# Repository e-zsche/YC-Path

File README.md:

# YC-Path

While most video synthesizers use an RGB to CVBS encoder IC for generating video signals the goal
of this project is to directly generate the luminance and chrominance signals used for analog
video signals.
of this project is to directly generate luminance and chrominance signals for analog video signals.

# System Overview

Module size specification is according to the doepfer eurorack standard.
<https://doepfer.de/a100_man/a100m_e.htm>
Module front plates are 3U in height and a multiple of 1HP wide with M3 mounting slots.

## Power Supply

The main power supply puts out ±5 V for all modules. Some older ICs run on +12V. To supply power
for these an auxilliary +12V rail is used.

First PSU Module uses Traco DC/DC Bricks. External Power is supplied via USB-C power delivery
at 20V.

TRACO TEN 10-2421:
- Vin: 18-36V
- Vout: +/- 5V
- Iout: +/- 1A

TRACO TSR 1-24120:
- Vin: 18-36V
- Vout: + 12V
- Iout: + 1A

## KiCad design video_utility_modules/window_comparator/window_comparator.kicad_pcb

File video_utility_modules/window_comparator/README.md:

# Window Comparator

Simple window comparator based on an LM319. Both thresholds are controllable by CV.

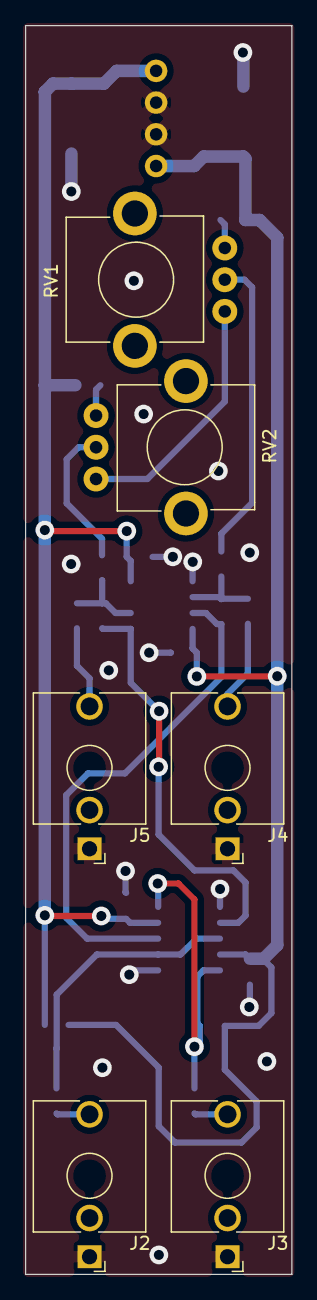
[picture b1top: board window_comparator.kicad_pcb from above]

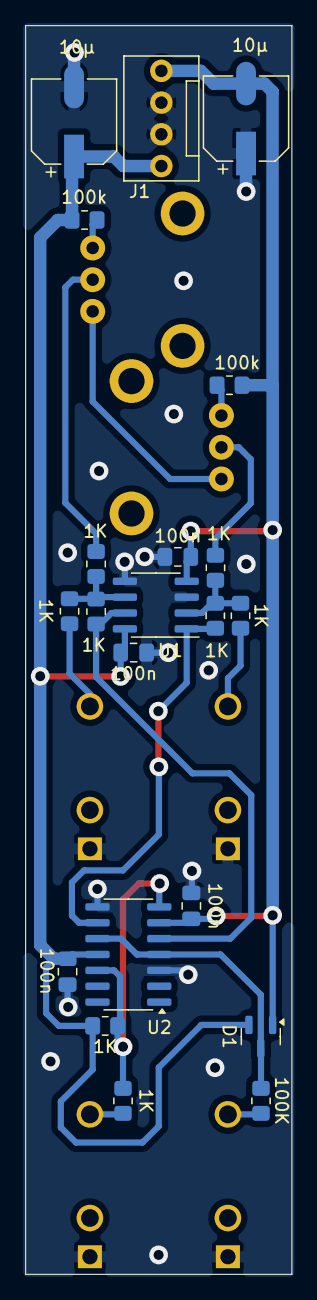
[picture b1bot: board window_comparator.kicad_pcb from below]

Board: 2 copper layers, 21.3 x 100.0 mm, 27 parts (21 on the bottom side), 18 nets.

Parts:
C1, C2, C5, C6: 100n; C_0805
C3, C4: 10µ; CP_Elec_6.3x5.3
D1: BAT54S; SOT-23
J1: pwr; pwr_conn_4pin
J2: In; Jack_3.5mm_QingPu_WQP-PJ398SM_Vertical_CircularHoles
J3: out; Jack_3.5mm_QingPu_WQP-PJ398SM_Vertical_CircularHoles
J4: CV lower; Jack_3.5mm_QingPu_WQP-PJ398SM_Vertical_CircularHoles
J5: CV upper; Jack_3.5mm_QingPu_WQP-PJ398SM_Vertical_CircularHoles
R1, R5, R9, R10, R11, R12, R13, R14: 1K; R_0805
R2, R3: 100k; R_0805
R4: 100K; R_0805
RV1, RV2: 25K; poti_stehend
U1: LMH6643; SOIC-8_no_mark
U2: LM319; SOIC-14_3.9x8.7mm_P1.27mm

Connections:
+5V: C1.1, C3.1, C5.1, D1.2 (K), J1.1, R1.1, R3.1, U1.8 (V+), U2.11 (V+)
-5V: C2.2, C4.2, C6.2, D1.1 (A), J1.4, R2.2, U1.4 (V-), U2.6 (V-)
/V_lower_pot: R12.1, RV1.2
/V_upper_pot: R14.1, RV2.2
/in: D1.3 (COM), R4.2, U2.4 (+), U2.10 (-)
/lower_tresh: R9.2, U1.7, U2.5 (-)
/out: J3.T, R5.2
/upper_tresh: R10.2, U1.1, U2.9 (+)
GND: C1.2, C2.1, C3.2, C4.1, C5.2, C6.1, J1.2, J1.3, J2.S, J3.S, J4.S, J5.S, U1.3 (+), U1.5 (+), U2.3 (GND), U2.8 (GND)
unnamed: J2.T, R4.1
unnamed: J4.T, R11.1
unnamed: J5.T, R13.1
unnamed: R1.2, R5.1, U2.7, U2.12
unnamed: R2.1, RV2.1
unnamed: R3.2, RV1.3
unnamed: RV1.1, RV2.3
unnamed: R10.1, R13.2, R14.2, U1.2 (-)
unnamed: R9.1, R11.2, R12.2, U1.6 (-)

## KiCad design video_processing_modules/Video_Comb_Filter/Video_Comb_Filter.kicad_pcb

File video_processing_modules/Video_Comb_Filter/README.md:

# Video Comb Filter

This module filters Luma and Chroma from an incoming CVBS signal. The filter is the obsolete
video IC SAA4960.

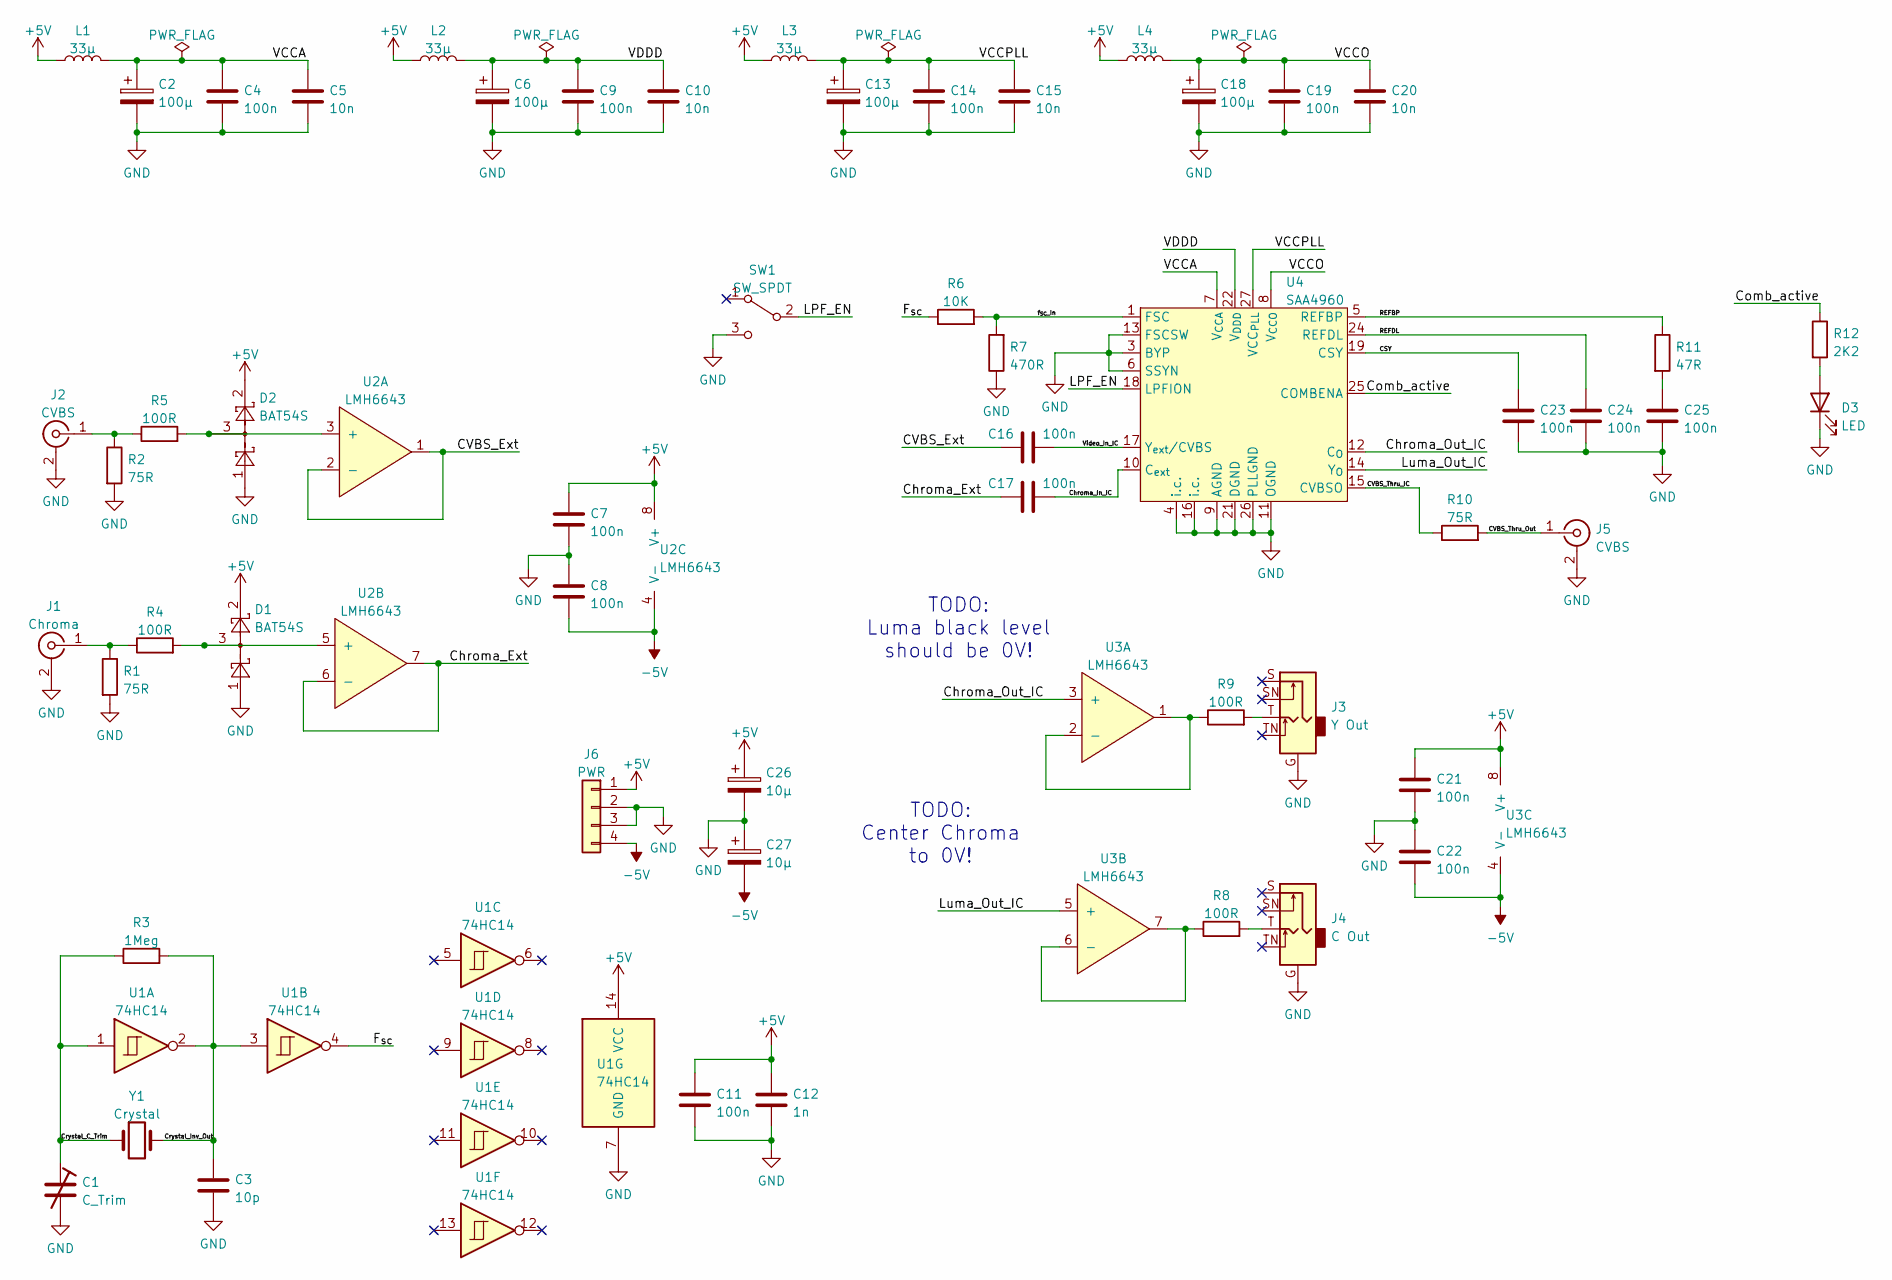
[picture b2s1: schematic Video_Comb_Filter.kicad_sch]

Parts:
C1: C_Trim
C2, C6, C13, C18: 100µ; CP_Radial_D8.0mm_P3.50mm
C3: 10p; C_0805
C4, C7, C8, C9, C11, C14, C16, C17, C19, C21, C22, C23, C24, C25: 100n; C_0805
C5, C10, C15, C20: 10n; C_0805
C12: 1n; C_0805
C26, C27: 10µ; CP_Radial_D8.0mm_P3.50mm
D1, D2: BAT54S; SOT-23
D3: LED; LED_D5.0mm
J1: Chroma; Cinch_Gewinkelt
J2: CVBS; Cinch_Gewinkelt
J3: Y Out; 3_5_mm_Buchse_EBS_35
J4: C Out; 3_5_mm_Buchse_EBS_35
J5: CVBS; BNC_Free
J6: PWR; pwr_conn_4pin
L1, L2, L3, L4: 33µ; Bourns SRN5040-330M
R1, R2, R10: 75R; R_0805
R3: 1Meg; R_0805
R4, R5, R8, R9: 100R; R_0805
R6: 10K; R_0805
R7: 470R; R_0805
R11: 47R; R_0805
R12: 2K2; R_0805
SW1: SW_SPDT; Schalter
U1: 74HC14; SOIC-14_no_mark
U2, U3: LMH6643; SOIC-8_no_mark
U4: SAA4960; DIP-28_W15.24mm_LongPads
Y1: Crystal; Crystal_HC49-U_Vertical

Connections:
+5V: C7.1, C11.1, C12.1, C21.1, C26.1, D1.2, D2.2, J6.1, L1.1, L2.1, L3.1, L4.1, U1.14 (VCC), U2.8 (V+), U3.8 (V+)
-5V: C8.2, C22.2, C27.2, J6.4, U2.4 (V-), U3.4 (V-)
/CSY: C23.1, U4.19 (CSY)
/CVBS_Ext: C16.1, U2.1, U2.2 (-)
/CVBS_Thru_IC: R10.1, U4.15 (CVBSO)
/CVBS_Thru_Out: J5.1 (In), R10.2
/Chroma_Ext: C17.1, U2.6 (-), U2.7
/Chroma_In_IC: C17.2, U4.10 (C_{ext})
/Chroma_Out_IC: U3.3 (+), U4.12 (C_{O})
/Comb_active: R12.1, U4.25 (COMBENA)
/Crystal_C_Trim: C1.1, R3.1, U1.1, Y1.1
/Crystal_Inv_Out: C3.1, R3.2, U1.2, U1.3, Y1.2
/F_{sc}: R6.1, U1.4
/LPF_EN: SW1.2 (B), U4.18 (LPFION)
/Luma_Out_IC: U3.5 (+), U4.14 (Y_{O})
/REFBP: R11.1, U4.5 (REFBP)
/REFDL: C24.1, U4.24 (REFDL)
/VCCA: C2.1, C4.1, C5.1, L1.2, U4.7 (V_{CCA})
/VCCO: C18.1, C19.1, C20.1, L4.2, U4.8 (V_{CCO})
/VCCPLL: C13.1, C14.1, C15.1, L3.2, U4.27 (VCC_{PLL})
/VDDD: C6.1, C9.1, C10.1, L2.2, U4.22 (V_{DDD})
/Video_In_IC: C16.2, U4.17 (Y_{ext}/CVBS)
/f_{SC}_In: R6.2, R7.2, U4.1 (FSC)
GND: C1.2, C2.2, C3.2, C4.2, C5.2, C6.2, C7.2, C8.1, C9.2, C10.2, C11.2, C12.2, C13.2, C14.2, C15.2, C18.2, C19.2, C20.2, C21.2, C22.1, C23.2, C24.2, C25.2, C26.2, C27.1, D1.1, D2.1, D3.1 (K), J1.2 (Ext), J2.2 (Ext), J3.G, J4.G, J5.2 (Ext), J6.2, J6.3, R1.2, R2.2, R7.1, SW1.3 (C), U1.7 (GND), U4.3 (BYP), U4.4 (i.c.), U4.6 (SSYN), U4.9 (AGND), U4.11 (OGND), U4.13 (FSCSW), U4.16 (i.c.), U4.21 (DGND), U4.26 (PLLGND)
unnamed: C25.1, R11.2
unnamed: D1.3, R4.2, U2.5 (+)
unnamed: D2.3, R5.2, U2.3 (+)
unnamed: D3.2 (A), R12.2
unnamed: J1.1 (In), R1.1, R4.1
unnamed: J2.1 (In), R2.1, R5.1
unnamed: J3.T, R9.2
unnamed: J4.T, R8.2
unnamed: R8.1, U3.6 (-), U3.7
unnamed: R9.1, U3.1, U3.2 (-)

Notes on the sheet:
TODO: Center Chroma to 0V!
TODO: Luma black level should be 0V!

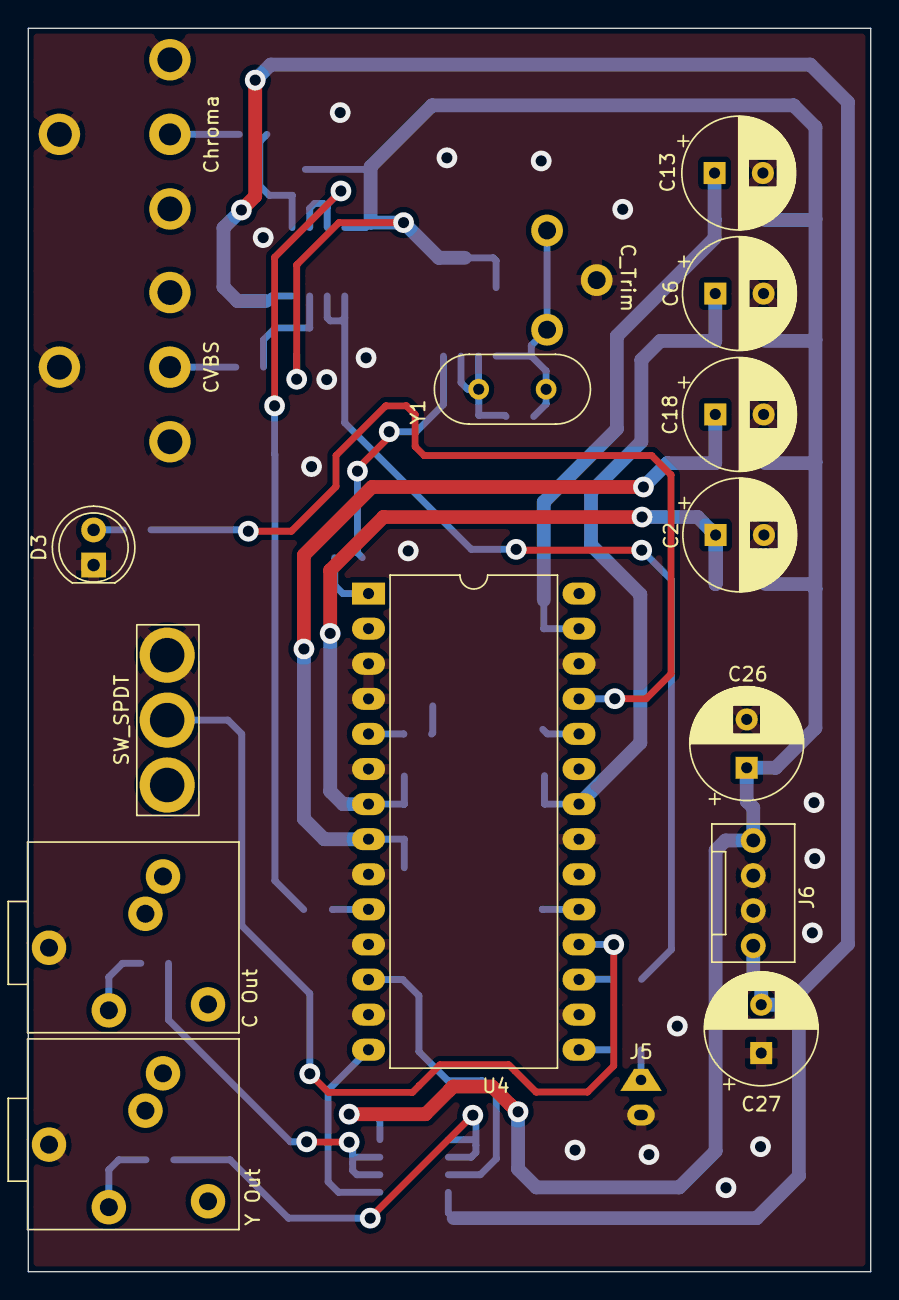
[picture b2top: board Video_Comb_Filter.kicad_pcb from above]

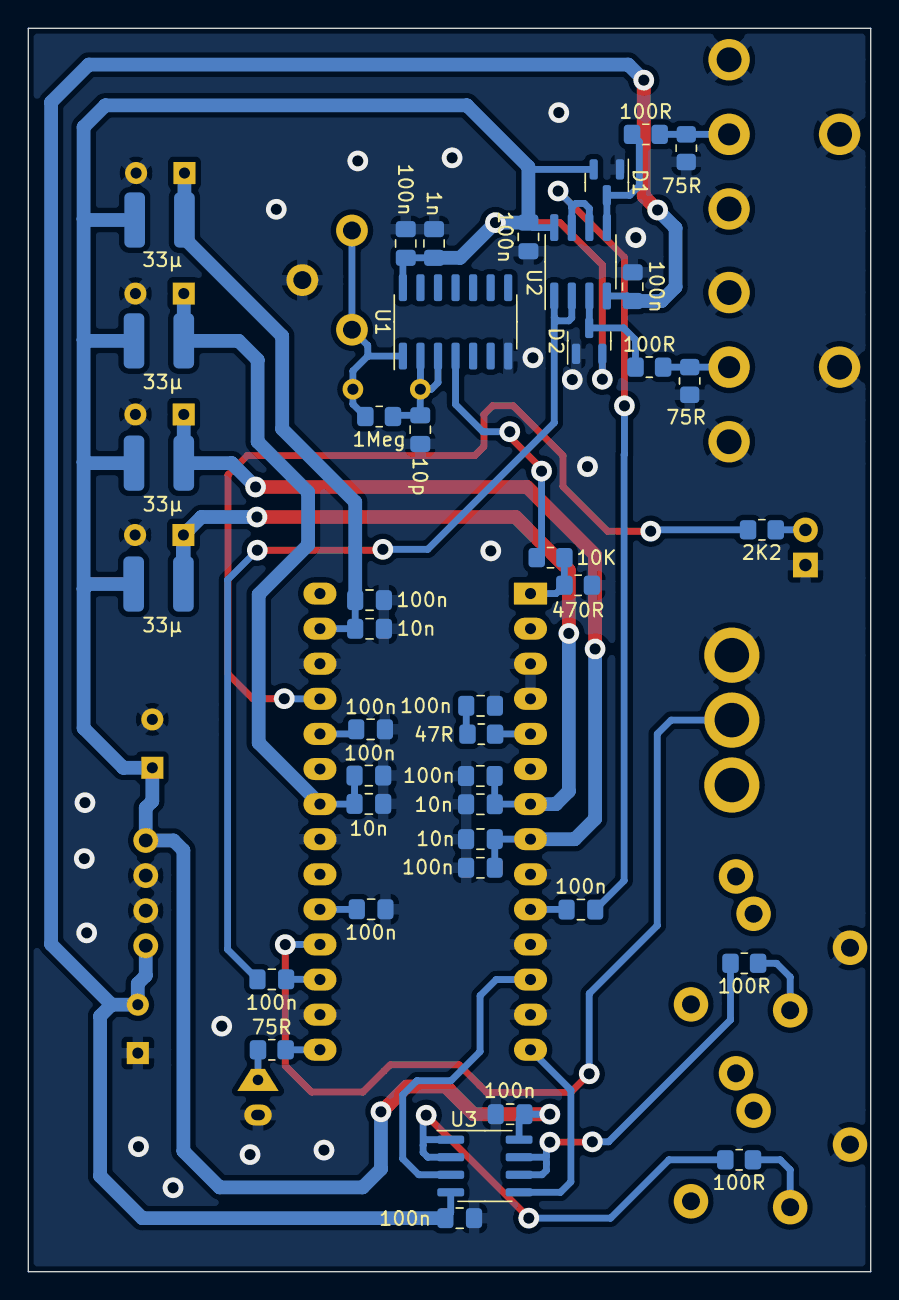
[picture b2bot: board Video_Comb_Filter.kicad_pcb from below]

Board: 2 copper layers, 61.0 x 90.0 mm, 58 parts (41 on the bottom side), 34 nets.

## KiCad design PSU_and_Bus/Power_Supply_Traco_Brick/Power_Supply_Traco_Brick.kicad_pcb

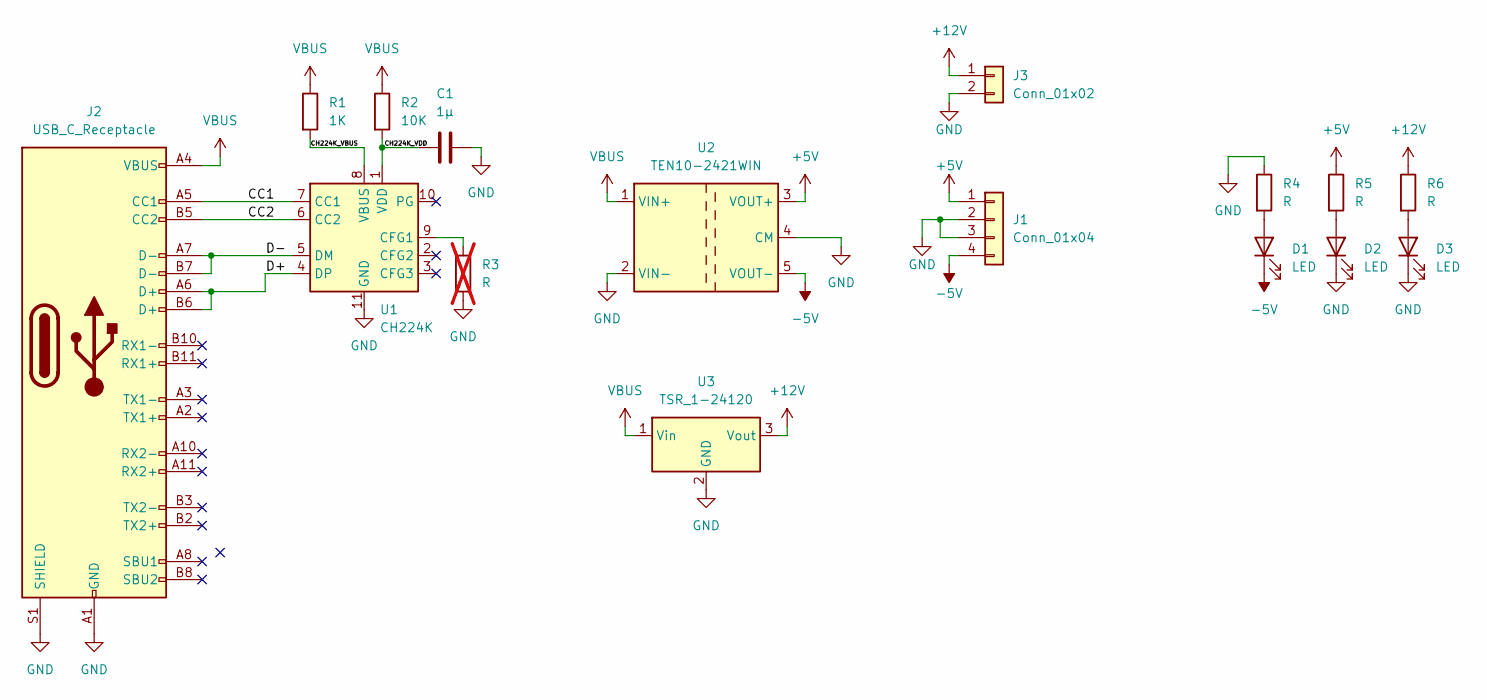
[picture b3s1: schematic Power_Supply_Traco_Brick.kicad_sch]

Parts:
C1: 1µ; C_0805
D1, D2, D3: LED; LED_D5.0mm
J1: Conn_01x04; PinHeader_1x04_P2.54mm_Vertical
J2: USB_C_Receptacle; USB_C_Receptacle_JAE_DX07S024WJ1R350
J3: Conn_01x02; PinHeader_1x02_P2.54mm_Vertical
R1: 1K; R_0805
R2: 10K; R_0805
R3: R; R_0805; not fitted
R4, R5, R6: R; R_0805
U1: CH224K; SSOP-10-1EP_3.9x4.9mm_P1mm_EP2.1x3.3mm
U2: TEN10-2421WIN; Converter_DCDC_TRACO_TEN10-xxxx_THT
U3: TSR_1-24120; Converter_DCDC_TRACO_TSR-1_THT

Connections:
+5V: J1.1, R5.1, U2.3 (VOUT+)
+12V: J3.1, R6.1, U3.3 (Vout)
-5V: D1.1 (K), J1.4, U2.5 (VOUT-)
/CC1: J2.A5 (CC1), U1.7 (CC1)
/CC2: J2.B5 (CC2), U1.6 (CC2)
/CH224K_VBUS: R1.2, U1.8 (VBUS)
/CH224K_VDD: C1.2, R2.2, U1.1 (VDD)
/D+: J2.A6 (D+), J2.B6 (D+), U1.4 (DP)
/D-: J2.A7 (D-), J2.B7 (D-), U1.5 (DM)
GND: C1.1, D2.1 (K), D3.1 (K), J1.2, J1.3, J2.A1 (GND), J2.A12 (GND), J2.B1 (GND), J2.B12 (GND), J2.S1 (SHIELD), J3.2, R3.2, R4.1, U1.11 (GND), U2.2 (VIN-), U2.4 (CM), U3.2 (GND)
unnamed: D1.2 (A), R4.2
unnamed: D2.2 (A), R5.2
unnamed: D3.2 (A), R6.2
unnamed: R3.1, U1.9 (CFG1)
VBUS: J2.A4 (VBUS), J2.A9 (VBUS), J2.B4 (VBUS), J2.B9 (VBUS), R1.1, R2.1, U2.1 (VIN+), U3.1 (Vin)

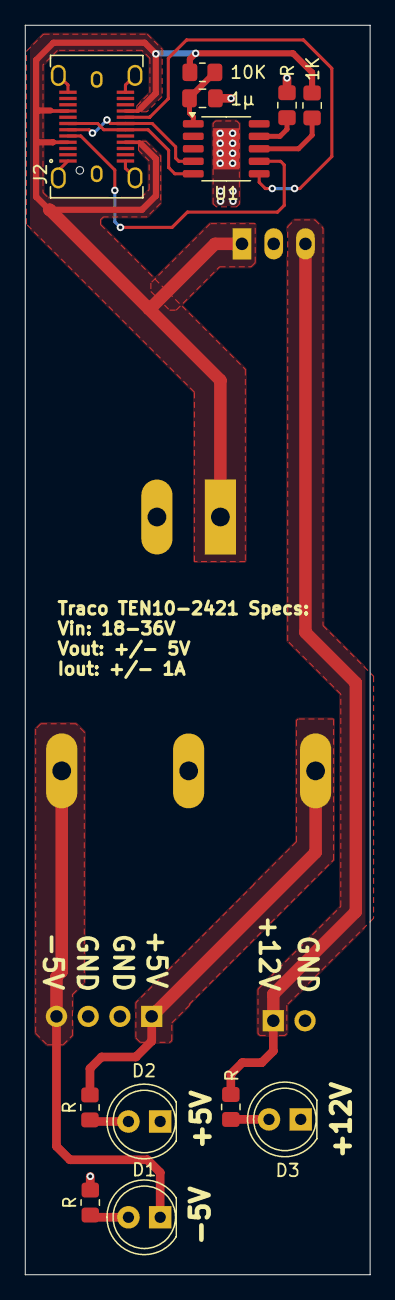
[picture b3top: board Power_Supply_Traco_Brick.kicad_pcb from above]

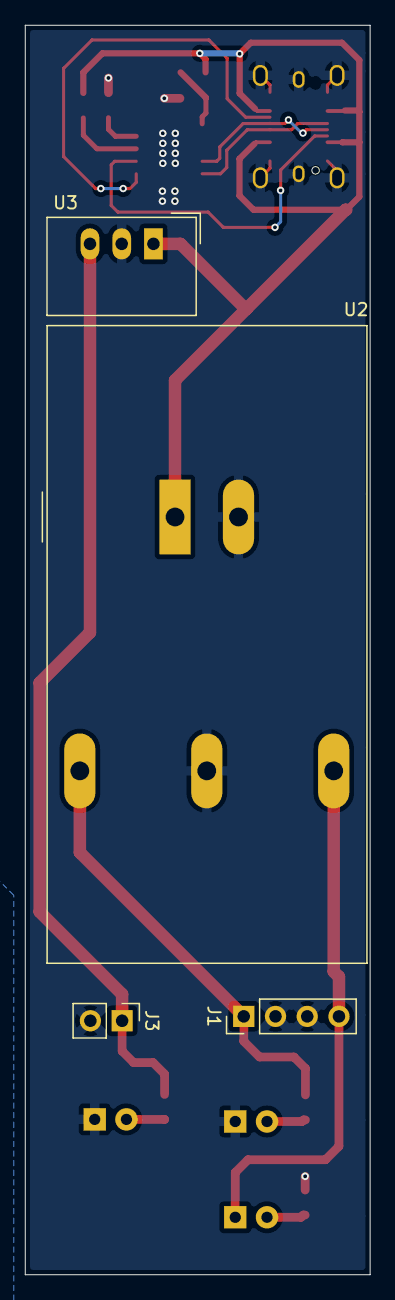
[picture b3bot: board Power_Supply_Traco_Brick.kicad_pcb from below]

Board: 2 copper layers, 27.6 x 100.0 mm, 16 parts (4 on the bottom side), 15 nets.

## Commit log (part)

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2025-07-22 SAA4960 Comb Filter
2025-07-22 window comparator module
2025-07-26 USB-C PD PSU with Traco Bricks
2025-07-26 README info on first power supply module
2025-07-26 fixed errors on PCB after DRC
    - Traces too close to PCB edge
    - overlap on F.Silkscreen
